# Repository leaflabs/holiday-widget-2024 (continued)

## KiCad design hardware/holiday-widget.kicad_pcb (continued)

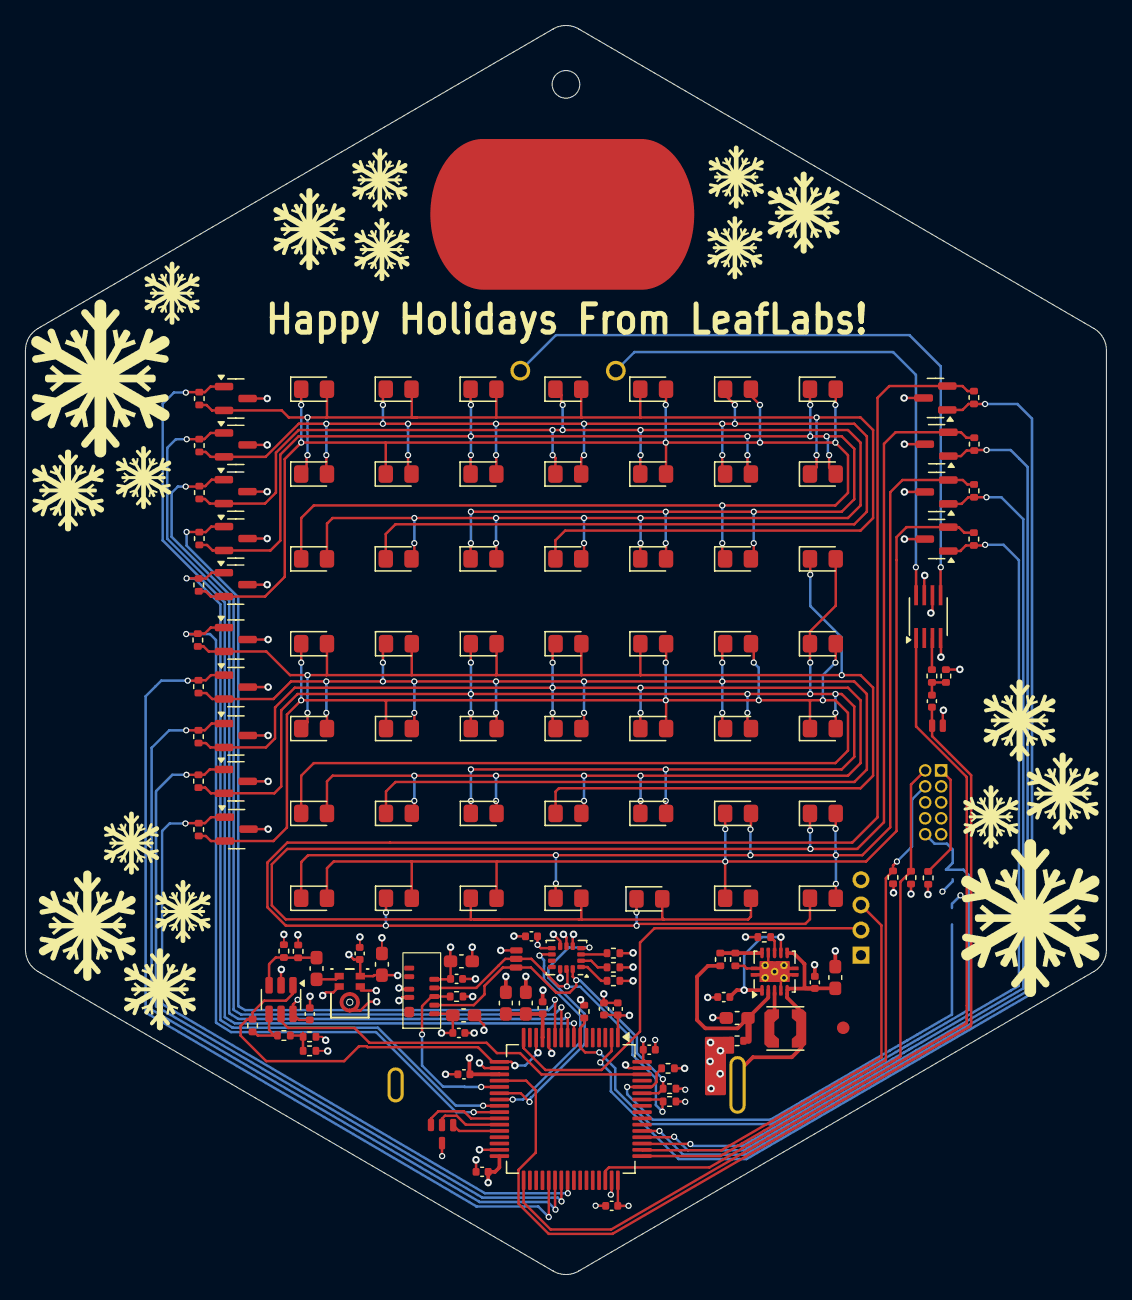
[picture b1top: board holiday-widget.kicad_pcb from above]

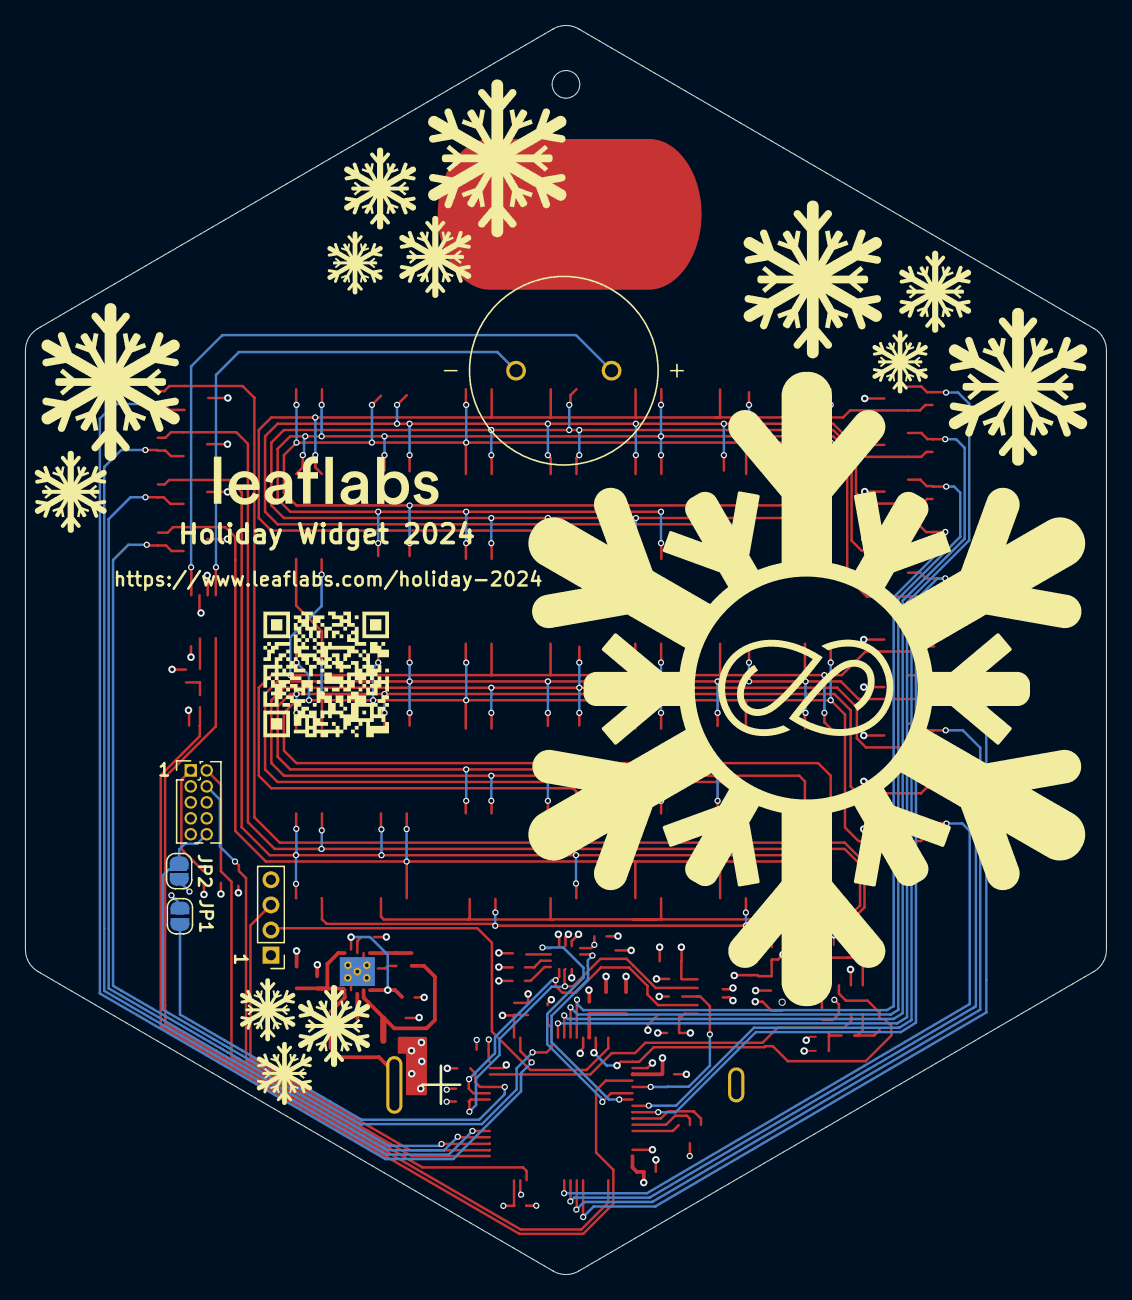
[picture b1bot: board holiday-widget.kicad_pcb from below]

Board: 4 copper layers, 86.0 x 99.4 mm, 146 parts (6 on the bottom side), 67 nets.

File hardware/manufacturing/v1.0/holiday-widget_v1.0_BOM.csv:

Comment,Designator,Footprint,JLCPCB Part #（optional）
,,,
STM32L072RBTx,U1,Package_QFP:LQFP-64_10x10mm_P0.5mm,C915968
TPS61200DRC,U2,Package_SON:Texas_S-PVSON-N10_ThermalVias,C140320
LIS3DH,U3,Package_LGA:LGA-16_3x3mm_P0.5mm_LayoutBorder3x5y,C15134
IMP23ABSU,U4,Leaf_Microphone:RHLGA5_3P5X2P65X0P98_STM,C3171746
TMP102xxDRL,U5,Package_TO_SOT_SMD:SOT-563,C99269
VCNL_4020,U6,Leaf_Sensor:VCNL4020_SMD,C511034
PAM8302AAD,U7,Package_SO:SSOP-8_2.95x2.8mm_P0.65mm,C113367
MMBT3906,"Q1,Q2,Q3,Q4,Q5,Q6,Q7,Q8",Package_TO_SOT_SMD:SOT-23,C2143
DNP,J1,,DNP
DNP,J2,,DNP
DNP,J3,,DNP
DNP,J4,,DNP
DNP,J5,,DNP
DNP,J6,,DNP
DNP,J7,,DNP
DNP,J33,,DNP
K2-1157SP-I4SW-01,"SW1,SW4",Button_Switch_SMD:SW_Push_1P1T_NO_6x6mm_H9.5mm,C2909692
Test Points,"TP1,TP2,TP3,TP4,TP5",Leaf_Jumper:TestPoint_0.5mm_1mm,DNP
Green LED,"D13, D19",LED_SMD:LED_0805_2012Metric_Pad1.15x1.40mm_HandSolder,C965816
Yellow LED,"D14, D15, D16, D20, D21, D22, D6, D8, D10, D26, D27, D28",LED_SMD:LED_0805_2012Metric_Pad1.15x1.40mm_HandSolder,C2296
Green LED,"D12, D17, D18, D9, D7, D5, D23, D24, D25, D11",LED_SMD:LED_0805_2012Metric_Pad1.15x1.40mm_HandSolder,C965816
Red LED,"D1, D2, D3, D4",LED_SMD:LED_0805_2012Metric_Pad1.15x1.40mm_HandSolder,C84256
50,"R15, R16, R17, R18, R19, R20, R21, R22",Resistor_SMD:R_0603_1608Metric_Pad0.98x0.95mm_HandSolder,
120,"R11,R12,R13,R14",Resistor_SMD:R_0603_1608Metric_Pad0.98x0.95mm_HandSolder,
10k,"R1,R2,R3,R6,R7,R8",Resistor_SMD:R_0603_1608Metric_Pad0.98x0.95mm_HandSolder,
1M,R4,Resistor_SMD:R_0603_1608Metric_Pad0.98x0.95mm_HandSolder,
180k,R5,Resistor_SMD:R_0603_1608Metric_Pad0.98x0.95mm_HandSolder,
0,"R9,R23,R24",Resistor_SMD:R_0603_1608Metric_Pad0.98x0.95mm_HandSolder,
100k,"R10,R25,R26",Resistor_SMD:R_0603_1608Metric_Pad0.98x0.95mm_HandSolder,
4.7u,C1,Capacitor_SMD:C_0603_1608Metric_Pad1.08x0.95mm_HandSolder,C1953079
10u,"C11,C15,C19,C23",Capacitor_SMD:C_0603_1608Metric_Pad1.08x0.95mm_HandSolder,C2959727
4.7u,C9,Capacitor_SMD:C_0603_1608Metric_Pad1.08x0.95mm_HandSolder,C108342
100n,"C2,C3,C4,C5,C7,C8,C10,C14,C17,C20, C21",Capacitor_SMD:C_0603_1608Metric_Pad1.08x0.95mm_HandSolder,C66501
1u,"C6,C13",Capacitor_SMD:C_0603_1608Metric_Pad1.08x0.95mm_HandSolder,C59302
1n,C12,Capacitor_SMD:C_0603_1608Metric_Pad1.08x0.95mm_HandSolder,C44369
22u,C16,Capacitor_SMD:C_0603_1608Metric_Pad1.08x0.95mm_HandSolder,C43922
10n,C18,Capacitor_SMD:C_0603_1608Metric_Pad1.08x0.95mm_HandSolder,C30926
LPS3015-222MRC,L1,Inductor_SMD:L_Coilcraft_LPS3010,C2844756

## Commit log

2024-05-15 Initial Commit.
2024-05-15 Ignore generated files and backups.
2024-05-18 [Hardware] v1.0 PCB
    Initial PCB design for holiday widget sent to JLCPCB.
2024-05-18 Add datasheets and STM32 documentation.
2024-05-28 Basic startup code for NUCLEO-L053R8 board.
    Added git submodule for STM32CubeL0 repo.
    Set up HAL library and added CMSIS functionality.
    Set up linker script and Makefile.
    Source code added to blink led when user button is pressed.
    Removed dependency on C library and added builtin functions required for compilation
2024-05-30 Fixed type issue for memset
2024-05-31 Added message logging using the uart. Added submodule for a smaller version of printf and friends. Uart code lives in separate file so only uart_logger_init() needs to be called before using uart_log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
2024-06-03 Moved low level init code to msp functions for organization
2024-06-04 Refactored code to use an interrupt file. Fixed issue where a HAL template file was overriding the default HAL clock implementation and using a different timer than the SysTick_Handler.
2024-06-05 Updated board specs so it can build properly
2024-06-05 Updated main to work with new board pinout
2024-06-05 Fix formatting
2024-06-07 Set up a basic I2C driver for the tmp102 sensor. Abstract out code for better readability. Add simple test to read temperature and print to the console every second
2024-06-12 Joshua/accelerometer
2024-06-14 Setup the vcnl4020 driver to measure proximity and ambient light value.
    Supports a user defined handler to process interrupts.
2024-06-17 Revamp the tmp102_driver to be more like the other sensors for configuration and for reading values.
    Add in configuration for how fast the sensor updates values.
2024-06-21 Add Charlieplexing to the holiday widget.
    Changes main's loop to just update LEDs for now.
2024-07-02 Add math library using lookup tables and a script to auto generate the tables.
2024-07-10 Convert i2c transactions to be non blocking. Implement a queue to hold i2c transactions and use futures for signaling when they are finished. Implement a job queue for an easy interface to cycle thro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
2024-07-10 Update uart to allow for adjustable baud rate
2024-07-10 Move state machines and setup functions to new files and clean up main.c
2024-07-11 Update bit_print to support arrays
2024-07-11 Update Makefile to remove all generated files/folders. Update Makefile to generate the filepath for the lut_generator binary Silence mkdir commands
2024-07-11 Update case statements to use braces for compliance Remove extra semicolons after functions Fix other warnings
2024-07-19 Add Charlieplexing to the job system. Simulate a 7x7 matrix and display the top 5x5 portion using the leds. Add led dimming. Add interface to setup frames to render. Improve Charlieplexing code to re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
2024-07-23 Add a script to take a series of images from a directory and save them in a header file. Allow for the user to still define their own animations. Adjust Makefile to auto build the animations. Provide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
2024-07-24 Add DMA music player to main - Implement low-level PAM8302A (audio amplifier) driver - Implement Music Player Core using timer and DMA to drive DAC output - Implement Music Player "wrapper" to allow 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
2024-07-24 Fix enum naming convention bug - Remove *_t suffix from enum Song_t in music_player_core.c - Remove *_t suffix from enum Song_t in music_player.c
2024-07-24 Prevent the Makefile from finishing if a generator script failed and deletes the generated file to require it to be built again
2024-07-24 Simplify I2C related initialization code Add low power mode to each driver
2024-07-26 Setup Docker CI Pipeline. - Add .gitlab-ci.yml with 'check' and 'build' stages - Add code-format Dockerfile for building image for 'check' stage - Add build-firmware Dockerfile for building image for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
2024-07-29 Remove temperature code from the widget project
2024-07-29 Correct Makefile and linker script. - Add `--print-memory-usage` flag for debug purposes - Change opencd target config file from `target/stm32l0.cfg` to `target/stm32l0_dual_bank.cfg` - Change FLASH 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
2024-08-05 Add a general state machine to control when other drivers are active Add interface for the general state machine to request data or change of states of other drivers
2024-08-06 Refactor music_player and related sub-systems away from singleton implementation. - All driver functions take a pointer to the driver instance as a parameter - All internal functions use snake_case -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
2024-08-06 Add led matrix to work with general state machine Make all led matrix functions independent of context and give control of their tasks to the general state machine Allow for selecting different anima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
2024-08-09 Add sprites and the ability to draw them to a buffer. Add communication between renderer and widget controller
2024-08-13 [Hardware] Update LEDs
    Add additional LEDs and arrange in 7x7 matrix. Remove 2x status LEDs. Reroute MCU connetions to be more sensible. Rearrange components.
2024-08-13 [Hardware] Remove unused breakouts
    * Remove extra GPIO and SPI outputs from MCU
    * remove auxillary connectors for GPIO, SPI, and I2C
2024-08-13 [Hardware] Replace LISDH Motion Sensor with LSM6DSM
    Change motion sensor to an accelerometer + gyro unit. Route the second interrupt line to the STM32.
2024-08-13 [Hardware] Remove tmp102
    No longer using the tmp102 temperature sensor, so remove it from the board.
2024-08-13 [Hardware] Add V2.0 Manufacturing files.
2024-08-13 [Hardware] Fix boot button pull-up resistor.
    Had an extra resistor, remove it.
2024-08-13 [Hardware] Boost converter updates.
    * Tie PS (power save) pin to ground to enable higher efficiencies during low-current operation
    * Add 0ohm resistor at output pin to measure current.
2024-08-13 [Hardware] Component changes.
    * Swap op-amp to similar and cheaper OPA504
    * Remove note about tantalum caps (per conversation w Alexa) and plan to replace in BOM with ceramic
2024-08-13 [Hardware] Add ferrite bead to VDDA. Swap schematic symbol for SWD-specific one. Add some notes to MCU pins.
2024-08-13 [Hardware] Add amplifier to microphone output.
    The STM32 part we are using does not include an internal opamp, so we are adding an external opamp to bias and amplify the audio signal.
    * Add opamp opa355
    * calculate resistor network for gain of 10
2024-08-13 [Hardware] Layout touchups for V2.
    Rearrange components mildly to increase density. Decrease footprint size slightly. Fix silkscreen.
2024-08-13 [Hardware] Update testpoints
    * Add TPs for I2C since we removed the I2C header
    * Add ground testpoints for GPIO and audio out
2024-08-13 [Hardware] Resize UART header to be 2.54mm pitch.
    Previous revision had incorrectly sized pinout, correct this.
2024-08-13 [Hardware] Update MCU pinout.
    * Move UART RX to PA15
    * Route audio input to PA3 in addition to PC0
2024-09-13 Neaten up the layout of the LED array
2024-09-13 Add KiRi support for viewing PCB diffs
2024-09-14 Change many passives to 0402 and assign part numbers
    Incorporate 0402 parts where possible
    Assign Manufacturer Part Numbers to parts where possible
    Update layout for the new passive sizes
2024-10-04 Organize source code into subdirectories
2024-10-04 Increase stack size from 8KB to 20KB
2024-10-04 Re-map charlieplex driver to new LED matrix layout
2024-10-04 Update IO to match hardware changes
2024-10-07 Offset LED index by +1 to compensate for DEFAULT_LED
2024-10-11 Remove status LEDs
2024-10-11 Replace buttons with jumper pads
2024-10-11 Add throughhole speaker
2024-10-11 Remove some silkscreen text
2024-10-11 Remove external power connector
2024-10-11 New hexagon routing.
2024-10-11 Tweak the logo size and placement
2024-10-11 Minor PCB graphics tweaking: Adjust logo letter spacing and update snowflake arrangement.
2024-10-11 Add a fiducial
2024-10-11 Add QR code and website to back silkscreen
2024-10-11 Add gerbers for v2.1 JLCPBC order
2024-12-05 - Re-map charlieplex driver to new LED matrix layout - Establish LSM6DSM functionality - Add interrupt-driven wrist tilt functionality - Add tilt interrupt source arbitration to determine the axis on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
2024-12-09 Add IMP23ABSU Driver
2024-12-09 Remove extraneous ampersand from i2c1_context.i2c.hdmarx and i2c1_context.i2c.hdmatx in DMA1_Channel4_5_6_7_IRQHandler
2024-12-10 Remove unused opacity field from struct entity.
2024-12-10 Remove unused boundary_conditions field from struct entity.
2024-12-10 Add additional helper functions to the ring buffer.
2024-12-10 Remove kinematics.c/h and shapes.c/h and move functionality to environment.h
2024-12-10 Use generic ring buffer for physics queue instead of custom implementation.
2024-12-10 Increase random_number_generator buffer size from 16 to 32 to avoid exhaustion.
2024-12-10 Abstract common game behavior, moving game state and event queue objects to a common struct.
2024-12-10 Format util.c
2024-12-10 Use generic ring buffer in uart logger.
2024-12-10 Add ARRAY_CONTAINS helper macro.
2024-12-10 Remove aligned attributes from entity struct fields.
2024-12-10 Return error code from random_number_generator_init().
2024-12-10 Remove unnecessary alignment attributes from random_number_generator fields.
2024-12-10 Encapsulate snowflake positioning logic into static helper functions.
2024-12-10 Remove commented out code and uneeded debug prints.
2024-12-10 Remove unnecessary volatile from physics_engine_collision_event fields.
2024-12-10 Remove unused physics_engine_config struct.
2024-12-10 Remove old optimization pragmas.
2024-12-10 Remove unecessary aligment attributes from struct vec2 and struct rectangle.
2024-12-10 Convert RING_BUFFER_INIT macro to ring_buffer_init function.
2024-12-10 Remove unnecessary alignment attributes from physics_engine_environment fields.
2024-12-10 Add NULL checks to game_entity_init.
2024-12-10 Remove unnecessary alignment attribute from struct ring_buffer.
2024-12-10 Remove redundant include of entity.h
2024-12-10 Update Makefile SRCS find command to include *.S files - allows arm_bitreversal2.S to be linked with source, needed for FFT.
2024-12-10 Create histogram bar sprite
2024-12-10 Re-order widget modes so that snowfall game is the first game mode
2024-12-10 Create FFT game.
2024-12-10 Insert FFT game into game engine and widget controller.
2024-12-10 Add entry/initial state to widget controller via the WIDGET_PREINIT state
2024-12-10 Remove unused vestigial WAKE_MS and SLEEP_MS macros
2024-12-10 Remove old comments
2024-12-10 Add support for entering and exiting low power mode when FFT game is active
2024-12-10 Correct system clock setup to use MSI and not HSI (was actually using MSI anyways since HSI wasn't properly configured anyways)
2024-12-10 Remove debug song 'SILENT_TEST_SOUND' from tones.h
2024-12-10 Add used attribute to sine_wave_volume_adj to suppress unused variable compiler warning
2024-12-10 Change scroll text 'scroll speed' implementation to use multiplication instead of bit shifting to achieve desirable speeds
2024-12-10 Remove debug prints and stale comments
2024-12-10 Remove old optimization pragmas
2024-12-10 Remove anti-aliasing functionality - resolution of LED matrix is too low for anti-aliasing to have a positive effect
2024-12-10 Correct 5x5 representation of the letter 'A'
2024-12-10 Removed old optimization pragmas
2024-12-10 Remove unnecessary includes
2024-12-10 Remove debug task from job queue - initial game state is now handled by widget controller so this is no longer necessary.
2024-12-10 Add curly braces to case statements
    On gcc toolchain 10.3.1, compilation fails due to "declarations after labels". Fix the
    case statements causing this problem.
2024-12-10 Remove unneeded casts in initializers to fix compiler complaints
    Some casts in initializers of static/global structures are not being correctly interpreted as constant on gcc 10.3.1. Remove these casts since they are redundant.
2024-12-10 Remove stale comment
2024-12-10 Fix interrupted scroll text bug
